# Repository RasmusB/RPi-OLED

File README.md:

# RPi-OLED Readme

Adapter board for using a generic OLED with a Raspberry Pi

> [!WARNING]
> Before using this repo, make sure to run the 'setup-hooks.sh' script first.

## Release notes

Releases are tagged using custom [Semantic Versioning rules](./Doc/SemVer%20Rules.md).

### 0.1.0

- TODO: List features that are introduced / removed
  - Focus on changes that would affect the end user, and indicate *how* they will be affected.
  - For example, don't write 'R2 changed to pull-down', but instead: 'Board will enter the bootloader when the user pushes SW1'.
  - More detailed change notes goes into the version history table in the schematic.

## Git behaviour

There are some pre-commit hooks in the .git folder. These will attempt to enforce a few sanity rules based on the following rules.

### The `main` branch must only contain releases of production files

- Commits to `main` are not allowed
- TODO: Commits must be tagged to generate production files (at least on the main branch)
- TODO: Tags must follow the pattern `vX.Y.Z` (see the [SemVer rules](./Doc/SemVer%20Rules.md) for details)

### Development happens in a `dev` branch

- All check-ins during development are made on the `dev` branch. The `dev` branch is merged into `main` when (and only when) the production files are ready for release.
- Any tags created on the dev branch *must not* match the pattern `vX.Y.Z` to ensure they are not confused for proper release tags
- Merging to main is not allowed if there are any failing tests (ERC, DRC, etc.)

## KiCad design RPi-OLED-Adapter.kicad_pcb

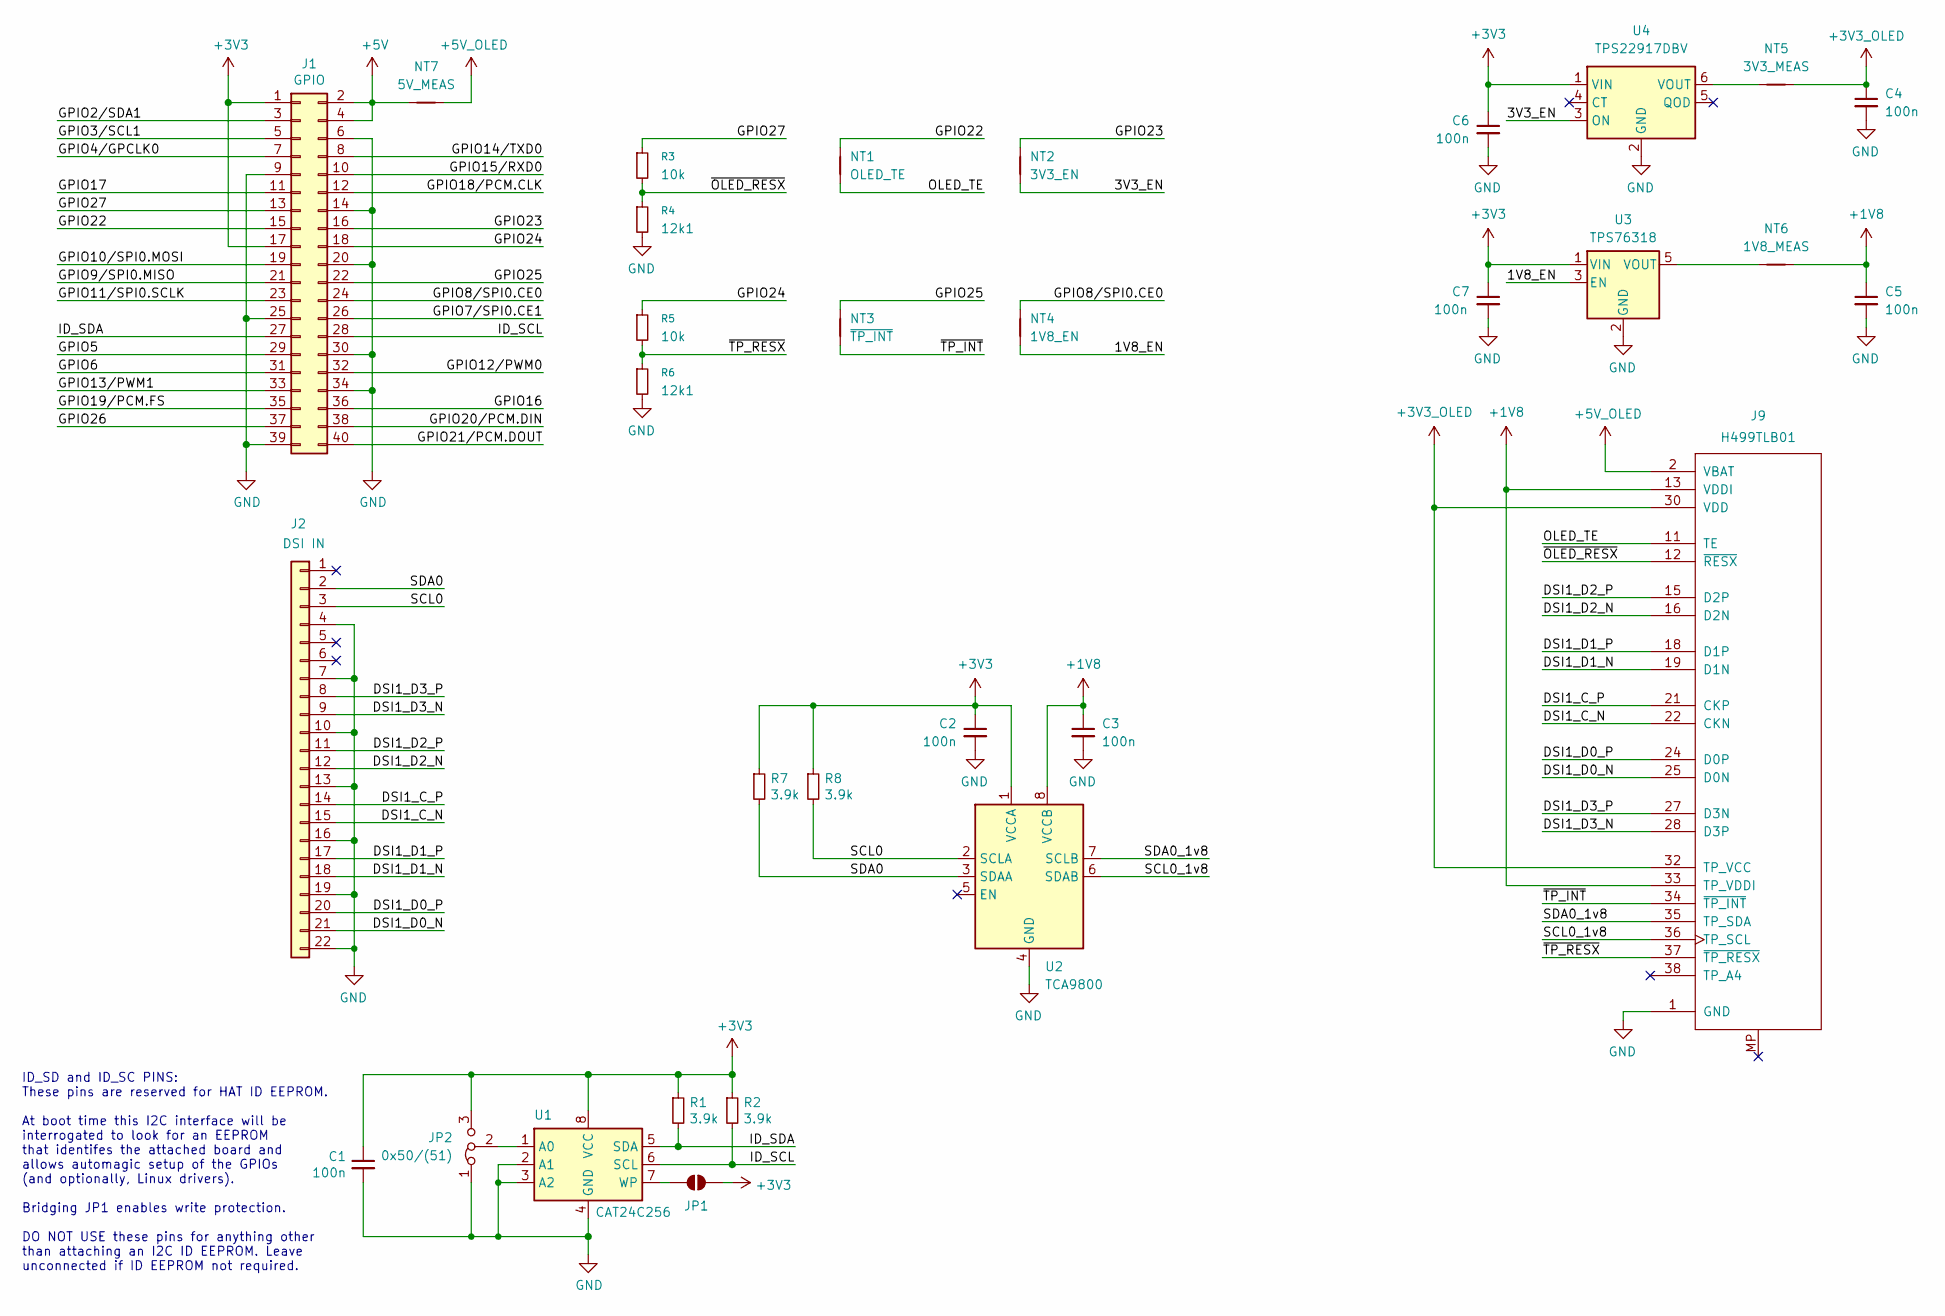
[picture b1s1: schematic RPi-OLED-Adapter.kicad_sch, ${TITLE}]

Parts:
C1, C2, C3, C4, C5, C6, C7: 100n; C_0402_1005Metric; MPN CL05B104KO5NNNC; LCSC Part # C1525
J1: GPIO; PinSocket_2x20_P2.54mm_Vertical; MPN 2541FV-2x20P-B; LCSC Part # C25503128
J2: DSI IN; Hirose_FH12-22S-0.5SH_1x22-1MP_P0.50mm_Horizontal; MPN FH12-22S-0.5SH(55); LCSC Part # C597981
J9: H499TLB01; Hirose_FH26-39S-0.3SHW_2Rows-39Pins-1MP_P0.60mm_Horizontal; MPN FH26W-39S-0.3SHW(60); LCSC Part # C92280
JP1: ID_WP; SolderJumper-2_P1.3mm_Bridged_RoundedPad1.0x1.5mm
JP2: 0x50/(51); SolderJumper-3_P1.3mm_Bridged12_RoundedPad1.0x1.5mm
NT1: OLED_TE; SolderJumper-2_P1.3mm_Bridged_RoundedPad1.0x1.5mm
NT2: 3V3_EN; SolderJumper-2_P1.3mm_Bridged_RoundedPad1.0x1.5mm
NT3: ~{TP_INT}; SolderJumper-2_P1.3mm_Bridged_RoundedPad1.0x1.5mm
NT4: 1V8_EN; SolderJumper-2_P1.3mm_Bridged_RoundedPad1.0x1.5mm
NT5: 3V3_MEAS; SolderJumper-2_P1.3mm_Bridged_RoundedPad1.0x1.5mm
NT6: 1V8_MEAS; SolderJumper-2_P1.3mm_Bridged_RoundedPad1.0x1.5mm
NT7: 5V_MEAS; SolderJumper-2_P1.3mm_Bridged_RoundedPad1.0x1.5mm
R1, R2, R7, R8: 3.9k; R_0402_1005Metric; MPN 0402WGJ0392TCE; LCSC Part # C11925
R3, R5: 10k; R_0402_1005Metric; MPN 0402WGJ0103TCE; LCSC Part # C25531
R4, R6: 12k1; R_0402_1005Metric; MPN 0402WGF1212TCE; LCSC Part # C25852
U1: CAT24C256; SOIC-8_5.3x5.3mm_P1.27mm; MPN CAT24C256WI-GT3; LCSC Part # C79987
U2: TCA9800; VSSOP-8_3x3mm_P0.65mm; MPN TCA9800DGKR; LCSC Part # C2677364
U3: TPS76318; SOT-23-5; MPN TPS76318DBVR; LCSC Part # C7099
U4: TPS22917DBV; SOT-23-6; MPN TPS22917DBVR; LCSC Part # C2681320

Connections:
+1V8: C3.1, C5.1, J9.13 (VDDI), J9.33 (TP_VDDI), NT6.2, U2.8 (VCCB)
+3V3: C1.1, C2.1, C6.1, C7.1, J1.1, J1.17, JP1.2 (B), JP2.3 (B), R1.1, R2.1, R7.1, R8.1, U1.8 (VCC), U2.1 (VCCA), U3.1 (VIN), U4.1 (VIN)
+3V3_OLED: C4.1, J9.30 (VDD), J9.32 (TP_VCC), NT5.2
+5V: J1.2, J1.4, NT7.1
+5V_OLED: J9.2 (VBAT), J9.3 (VBAT), J9.4 (VBAT), J9.5 (VBAT), J9.6 (VBAT), NT7.2
/1V8_EN: NT4.1, U3.3 (EN)
/3V3_EN: NT2.1, U4.3 (ON)
/DSI1_C_N: J2.15, J9.22 (CKN)
/DSI1_C_P: J2.14, J9.21 (CKP)
/DSI1_D0_N: J2.21, J9.25 (D0N)
/DSI1_D0_P: J2.20, J9.24 (D0P)
/DSI1_D1_N: J2.18, J9.19 (D1N)
/DSI1_D1_P: J2.17, J9.18 (D1P)
/DSI1_D2_N: J2.12, J9.16 (D2N)
/DSI1_D2_P: J2.11, J9.15 (D2P)
/DSI1_D3_N: J2.9, J9.28 (D3P)
/DSI1_D3_P: J2.8, J9.27 (D3N)
/GPIO2/SDA1: J1.3
/GPIO3/SCL1: J1.5
/GPIO4/GPCLK0: J1.7
/GPIO5: J1.29
/GPIO6: J1.31
/GPIO7/SPI0.CE1: J1.26
/GPIO8/SPI0.CE0: J1.24, NT4.2
/GPIO9/SPI0.MISO: J1.21
/GPIO10/SPI0.MOSI: J1.19
/GPIO11/SPI0.SCLK: J1.23
/GPIO12/PWM0: J1.32
/GPIO13/PWM1: J1.33
/GPIO14/TXD0: J1.8
/GPIO15/RXD0: J1.10
/GPIO16: J1.36
/GPIO17: J1.11
/GPIO18/PCM.CLK: J1.12
/GPIO19/PCM.FS: J1.35
/GPIO20/PCM.DIN: J1.38
/GPIO21/PCM.DOUT: J1.40
/GPIO22: J1.15, NT1.2
/GPIO23: J1.16, NT2.2
/GPIO24: J1.18, R5.1
/GPIO25: J1.22, NT3.2
/GPIO26: J1.37
/GPIO27: J1.13, R3.1
/ID_SCL: J1.28, R2.2, U1.6 (SCL)
/ID_SDA: J1.27, R1.2, U1.5 (SDA)
/OLED_TE: J9.11 (TE), NT1.1
/SCL0: J2.3, R8.2, U2.2 (SCLA)
/SCL0_1v8: J9.36 (TP_SCL), U2.6 (SDAB)
/SDA0: J2.2, R7.2, U2.3 (SDAA)
/SDA0_1v8: J9.35 (TP_SDA), U2.7 (SCLB)
/~OLED_RESX: J9.12 (~RESX), R3.2, R4.1
/~TP_INT: J9.34 (~TP_INT), NT3.1
/~TP_RESX: J9.37 (~TP_RESX), R5.2, R6.1
GND: C1.2, C2.2, C3.2, C4.2, C5.2, C6.2, C7.2, J1.6, J1.9, J1.14, J1.20, J1.25, J1.30, J1.34, J1.39, J2.4, J2.7, J2.10, J2.13, J2.16, J2.19, J2.22, J9.1 (GND), J9.7 (GND), J9.8 (GND), J9.9 (GND), J9.14 (GND), J9.17 (GND), J9.20 (GND), J9.23 (GND), J9.26 (GND), J9.29 (GND), J9.31 (GND), J9.39 (GND), JP2.1 (A), R4.2, R6.2, U1.2 (A1), U1.3 (A2), U1.4 (GND), U2.4 (GND), U3.2 (GND), U4.2 (GND)
unnamed: JP1.1 (A), U1.7 (WP)
unnamed: JP2.2 (C), U1.1 (A0)
unnamed: NT6.1, U3.5 (VOUT)
unnamed: NT5.1, U4.6 (VOUT)

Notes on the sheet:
ID_SD and ID_SC PINS: These pins are reserved for HAT ID EEPROM. At boot time this I2C interface will be interrogated to look for an EEPROM that identifes the attached board and allows automagic setup of the GPIOs (and optionally, Linux drivers). Bridging JP1 enables write protection. DO NOT USE th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

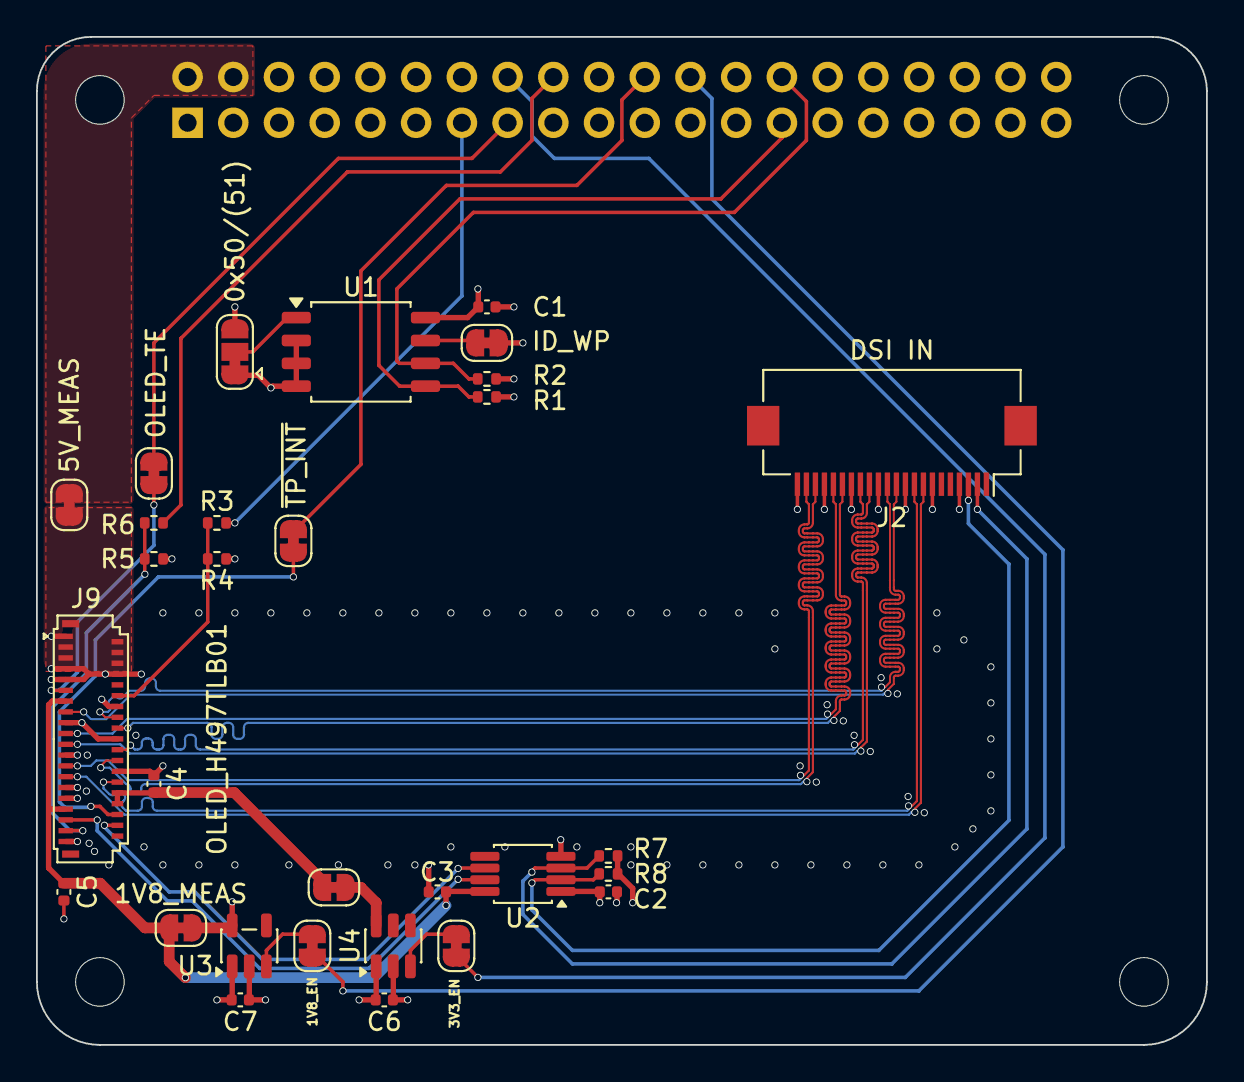
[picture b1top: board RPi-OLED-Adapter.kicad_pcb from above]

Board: 4 copper layers, 65.0 x 56.0 mm, 35 parts (1 on the bottom side), 38 nets.

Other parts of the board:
MH1, MH2, MH3, MH4: MountingHole_2.7mm_M2.5

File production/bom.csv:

Designator,Footprint,Quantity,Value,LCSC Part #
"C1, C2, C3, C4, C5, C6, C7",0402,7,100n,C1525
J1,PinSocket_2x20_P2.54mm_Vertical,1,GPIO,
J2,Hirose_FH12-22S-0.5SH_1x22-1MP_P0.50mm_Horizontal,1,DSI IN,C597981
J9,Hirose_FH26-39S-0.3SHW_2Rows-39Pins-1MP_P0.60mm_Horizontal,1,OLED_H497TLB01,C92280
"R1, R2, R7, R8",0402,4,3.9k,C11925
"R3, R5",0402,2,10k,C25531
"R4, R6",0402,2,12k1,C25852
U1,SOIC-8_5.3x5.3mm_P1.27mm,1,CAT24C256,C79987
U2,VSSOP-8_3x3mm_P0.65mm,1,TCA9800,C2677364
U3,SOT-23-5,1,TPS76318,C7099
U4,SOT-23-6,1,TPS22917DBV,C2681320
